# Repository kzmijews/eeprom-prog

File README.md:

# EEPROM programer

## Overview
EEPROM programer dedicated for AT28C16 memory.
Electrical schema was created in [EAGLE](https://www.autodesk.com/products/eagle/overview):

<div>
    
    <p align="center">
        <i>Figure 1.1: EEPROM prog schema</i>
    </p>
</div>

Same as board design:

<div>
    
    <p align="center">
        <i>Figure 1.2: top layer of EEPROM prog board</i>
    </p>
</div>

<div>
    
    <p align="center">
        <i>Figure 1.3: bottom layer of EEPROM prog board</i>
    </p>
</div>

It was done based on Arduino Nano 3.0 (ATmega328P):

<div>
    
    <p align="center">
        <i>Figure 1.4: Possible implementation on prototype board</i>
    </p>
</div>

Software library is written in C++, and it's available in `code/eeprom`.
To use it copy `eeprom` folder into your sketch directory (to check directory from [Arduino IDE](https://www.arduino.cc/en/software):
go into: File -> Preferences -> Settings -> Sketchbook location), and load it (Sketch -> Include Library -> eeprom). It will add
"include <eeprom.h>" header file to your project.

## Usage
Available API:
- **begin()**: configure pins and serial output
- **setAddress(unsigned int address, bool rw_bit)**: choose memory address to perform action over the pointed cell
- **read(unsigned int address)**: read byte of data from memory address
- **write(unsigned int address, byte data)**: write byte of data under memory address
- **print(byte data_row_size, unsigned int data_total_size)**: print on serial output (COM) piece of memory content
- **clean()**: write whole memory chip with value 0x00
- **erase()**: erase whole memory chip by writing 0xFF
- **writeAll(byte value)**: write whole memory chip with given value

Example:
```cpp
#include <eeprom.h>

EEPROM eeprom;

void setup() {
    // configure library
    eeprom.begin();
    // write byte (0x01) of data at address 0x00
    eeprom.write(0x00, 0x01);
    // print two rows of data (16 bytes per row, 32 bytes in total)
    eeprom.print(16, 32);
    // read single byte of data from address
    byte read_data = eeprom.read(0x00);
}

void loop() {
}
```

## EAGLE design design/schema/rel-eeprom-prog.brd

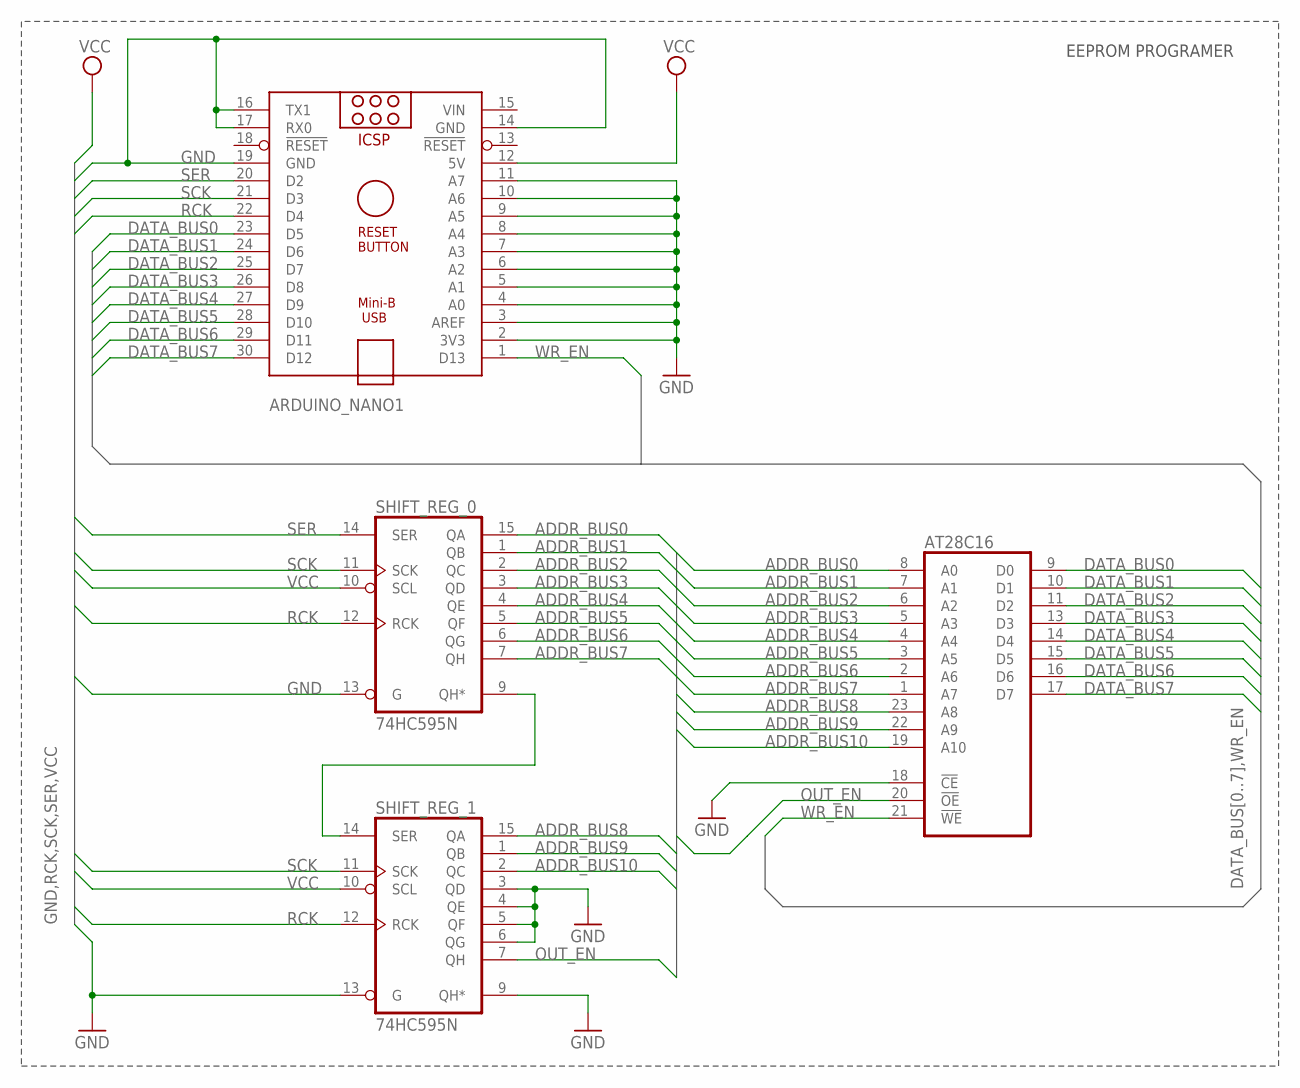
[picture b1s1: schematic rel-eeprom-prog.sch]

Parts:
ARDUINO_NANO1: ARDUINO_NANO
AT28C16: 2816; DIL24
SHIFT_REG_0, SHIFT_REG_1: 74HC595N; DIL16

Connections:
ADDR_BUS0: AT28C16.8 (A0), SHIFT_REG_0.15 (QA)
ADDR_BUS1: AT28C16.7 (A1), SHIFT_REG_0.1 (QB)
ADDR_BUS2: AT28C16.6 (A2), SHIFT_REG_0.2 (QC)
ADDR_BUS3: AT28C16.5 (A3), SHIFT_REG_0.3 (QD)
ADDR_BUS4: AT28C16.4 (A4), SHIFT_REG_0.4 (QE)
ADDR_BUS5: AT28C16.3 (A5), SHIFT_REG_0.5 (QF)
ADDR_BUS6: AT28C16.2 (A6), SHIFT_REG_0.6 (QG)
ADDR_BUS7: AT28C16.1 (A7), SHIFT_REG_0.7 (QH)
ADDR_BUS8: AT28C16.23 (A8), SHIFT_REG_1.15 (QA)
ADDR_BUS9: AT28C16.22 (A9), SHIFT_REG_1.1 (QB)
ADDR_BUS10: AT28C16.19 (A10), SHIFT_REG_1.2 (QC)
CARRY: SHIFT_REG_0.9 (QH*), SHIFT_REG_1.14 (SER)
DATA_BUS0: ARDUINO_NANO1.23 (D5), AT28C16.9 (D0)
DATA_BUS1: ARDUINO_NANO1.24 (D6), AT28C16.10 (D1)
DATA_BUS2: ARDUINO_NANO1.25 (D7), AT28C16.11 (D2)
DATA_BUS3: ARDUINO_NANO1.26 (D8), AT28C16.13 (D3)
DATA_BUS4: ARDUINO_NANO1.27 (D9), AT28C16.14 (D4)
DATA_BUS5: ARDUINO_NANO1.28 (D10), AT28C16.15 (D5)
DATA_BUS6: ARDUINO_NANO1.29 (D11), AT28C16.16 (D6)
DATA_BUS7: ARDUINO_NANO1.30 (D12), AT28C16.17 (D7)
GND: ARDUINO_NANO1.2 (3V3), ARDUINO_NANO1.3 (AREF), ARDUINO_NANO1.4 (A0), ARDUINO_NANO1.5 (A1), ARDUINO_NANO1.6 (A2), ARDUINO_NANO1.7 (A3), ARDUINO_NANO1.8 (A4), ARDUINO_NANO1.9 (A5), ARDUINO_NANO1.10 (A6), ARDUINO_NANO1.11 (A7), ARDUINO_NANO1.14 (GND), ARDUINO_NANO1.16 (TX1), ARDUINO_NANO1.17 (RX0), ARDUINO_NANO1.19 (GND), AT28C16.12 (GND), AT28C16.18 (!CE), SHIFT_REG_0.8 (GND), SHIFT_REG_0.13 (G), SHIFT_REG_1.3 (QD), SHIFT_REG_1.4 (QE), SHIFT_REG_1.5 (QF), SHIFT_REG_1.6 (QG), SHIFT_REG_1.8 (GND), SHIFT_REG_1.9 (QH*), SHIFT_REG_1.13 (G)
OUT_EN: AT28C16.20 (!OE), SHIFT_REG_1.7 (QH)
RCK: ARDUINO_NANO1.22 (D4), SHIFT_REG_0.12 (RCK), SHIFT_REG_1.12 (RCK)
SCK: ARDUINO_NANO1.21 (D3), SHIFT_REG_0.11 (SCK), SHIFT_REG_1.11 (SCK)
SER: ARDUINO_NANO1.20 (D2), SHIFT_REG_0.14 (SER)
VCC: ARDUINO_NANO1.12 (5V), AT28C16.24 (VCC), SHIFT_REG_0.10 (SCL), SHIFT_REG_0.16 (VCC), SHIFT_REG_1.10 (SCL), SHIFT_REG_1.16 (VCC)
VIN: ARDUINO_NANO1.15 (VIN)
WR_EN: ARDUINO_NANO1.1 (D13), AT28C16.21 (!WE)

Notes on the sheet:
EEPROM PROGRAMER

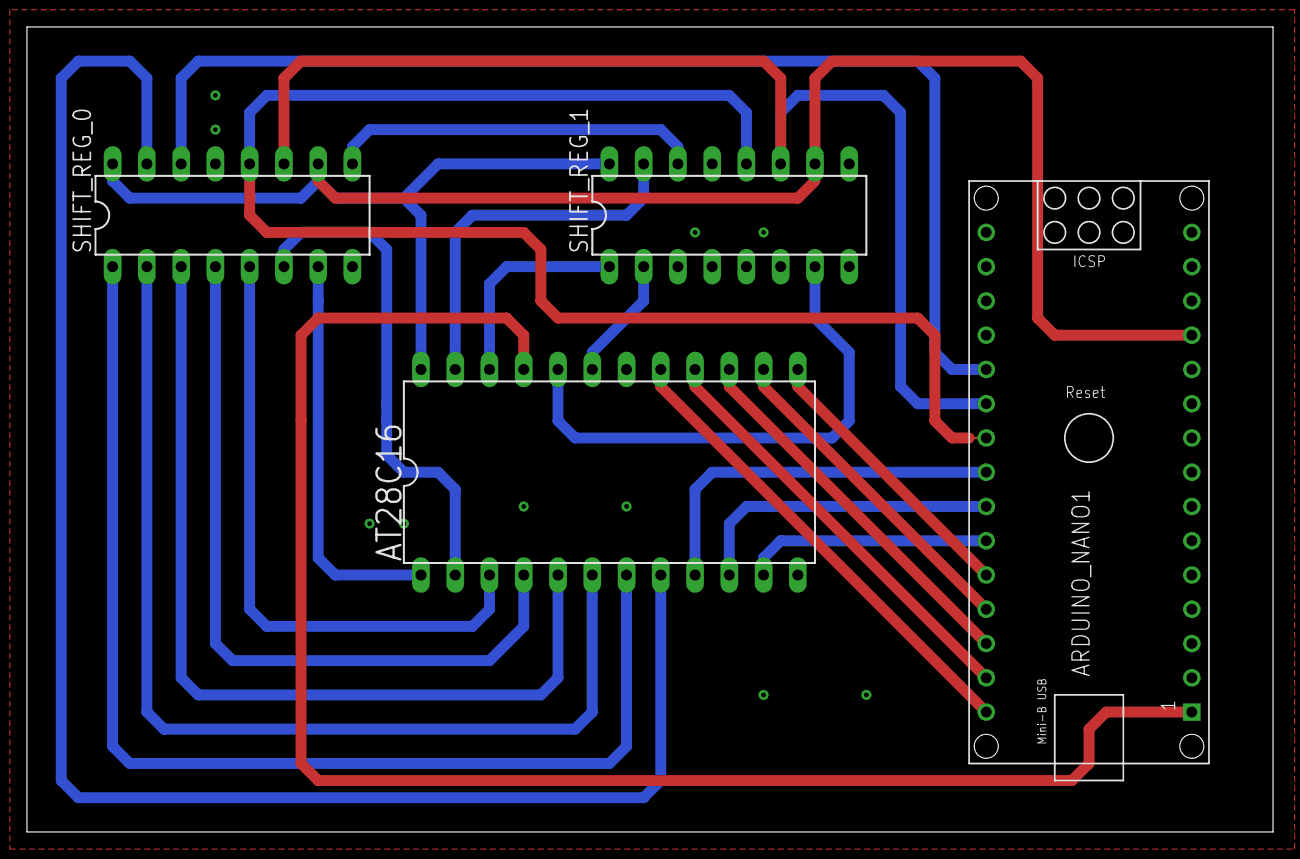
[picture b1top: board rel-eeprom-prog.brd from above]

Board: 2 copper layers, 92.4 x 59.7 mm, 4 parts (0 on the bottom side), 27 nets.

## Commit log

2024-05-30 Added initial version of EEPROM programer
2024-05-30 Add short description for README.md file
2024-05-30 Fixed for improper pull down on SCL pin
2024-05-30 Fixed serial output configuration
2024-05-30 Renamed API functions
2024-05-31 Updated README.md file for the project
2024-05-31 Fixed code block for README.md
2024-05-31 Removed surpluis quote marks
2024-05-31 Added initial version of board design
2024-06-03 Updated IC chips names
2024-06-10 Added erase and writeAll API methods
2024-07-14 Created LICENSE.md
